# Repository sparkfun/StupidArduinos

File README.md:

# StupidArduinos

Stupid Arduino is the practice of designing elaborate and pointless implementations of the Arduino platform. I chose Arduino as the phrase on which I would be free-style improvising for a few reasons. First of all, it’s a popular and accessible platform — far fewer people would be excited about stupid implementations of, say, HyperCard. Secondly, the ingredients for an “Arduino” (in the generic sense) are few and well defined: Any microcontroller with accessible GPIO running the Arduino bootloader can be reasonably referred to as an Arduino. And finally, it’s a platform that comprises multiple disciplines: An Arduino can be “stupid” because of its controller, its electrical design, its mechanical design or even its firmware or bootloader design. 

Stupid Arduino only has three rules: 

1) The device must run a functional, Arduino-flavored bootloader
2) It has to execute the example “blink” sketch (with appropriate delays)
3) It must have some form of GPIO broken out from the controller

Beyond that, anything goes: fun clock speeds, clock sources, architectures, form factors, power management - it’s all fair game.

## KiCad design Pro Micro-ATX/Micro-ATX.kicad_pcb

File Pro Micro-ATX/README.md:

<h2>The RedBoard Pro Micro-ATX</h2>

Let me show you its features:

1) Convenient and well-supported Micro-ATX form factor

The Micro-ATX form factor is compatible not only with Micro-ATX PC cases but also Standard- and Extended-ATX cases. The Pro Micro-ATX conforms to the mechanical specs for footprint size, stand-off placement and expansion card position for the widest possible compatibility across case manufacturers.

2) Support for enthusiast-grade cooling hardware

The heart of the Pro Micro-ATX is an ATmega32u4 microcontroller that has been positioned (along with the necessary support components) within the mechanical footprint of an LGA 1151 socket. This gives the user a wide array of options for (pointlessly) cooling the microcontroller, including many AIO air and liquid coolers designed for modern Intel processors.

3) 24-pin ATX power support

Arguably the only useful feature on this board is the 24-pin power connector, which allows the ATmega32u4 and its peripherals to draw from any external, ATX-compatible power supply.

4) Expanded EEPROM

You may be surprised to find that I had, uh, some room on the board. I decided that one way of utilizing this space might be to stack as many I²C EEPROM chips as I could on the one available bus. That number turns out to be eight (with capacities up to 512k), giving this board a whopping 2Mbits of storage! I stopped just short of Shawn’s suggestion of laying out I²C DIMM footprints and compatible “RAM cards,” because you have to draw the line somewhere…

5) Card Slots!!!

…but NOT at expansion cards! After all, what’s a motherboard layout without expansion slots? It’s not enthusiast-grade, that’s for sure. So I created a system of expansion cards for the Pro Micro-ATX. It could be argued that the Arduino already has a system of expansion cards — shields — and that they are the best possible expansion system given that they have access to literally every I/O of the host controller. I decided that there was no electrical improvement to be made here and that, instead, adapting the shield system to the ATX form factor would be my main focus. I found the idea of using PCI connectors a little excessive, even for an undertaking of this magnitude, and opted for a smaller 28 Position Card Edge Connector. The compatible cards adapt the pinout of the edge connector back to the familiar Arduino shield form factor, so any existing shield can be connected and accessed through the expansion slots in the back of the case.

6) Rear I/O

Any good motherboard has rear I/O and the Pro Micro-ATX is no exception. Accessible from the rear panel are a standard shield footprint, a 6-pin Atmel ISP header and a USB type-B connector for serial communication.

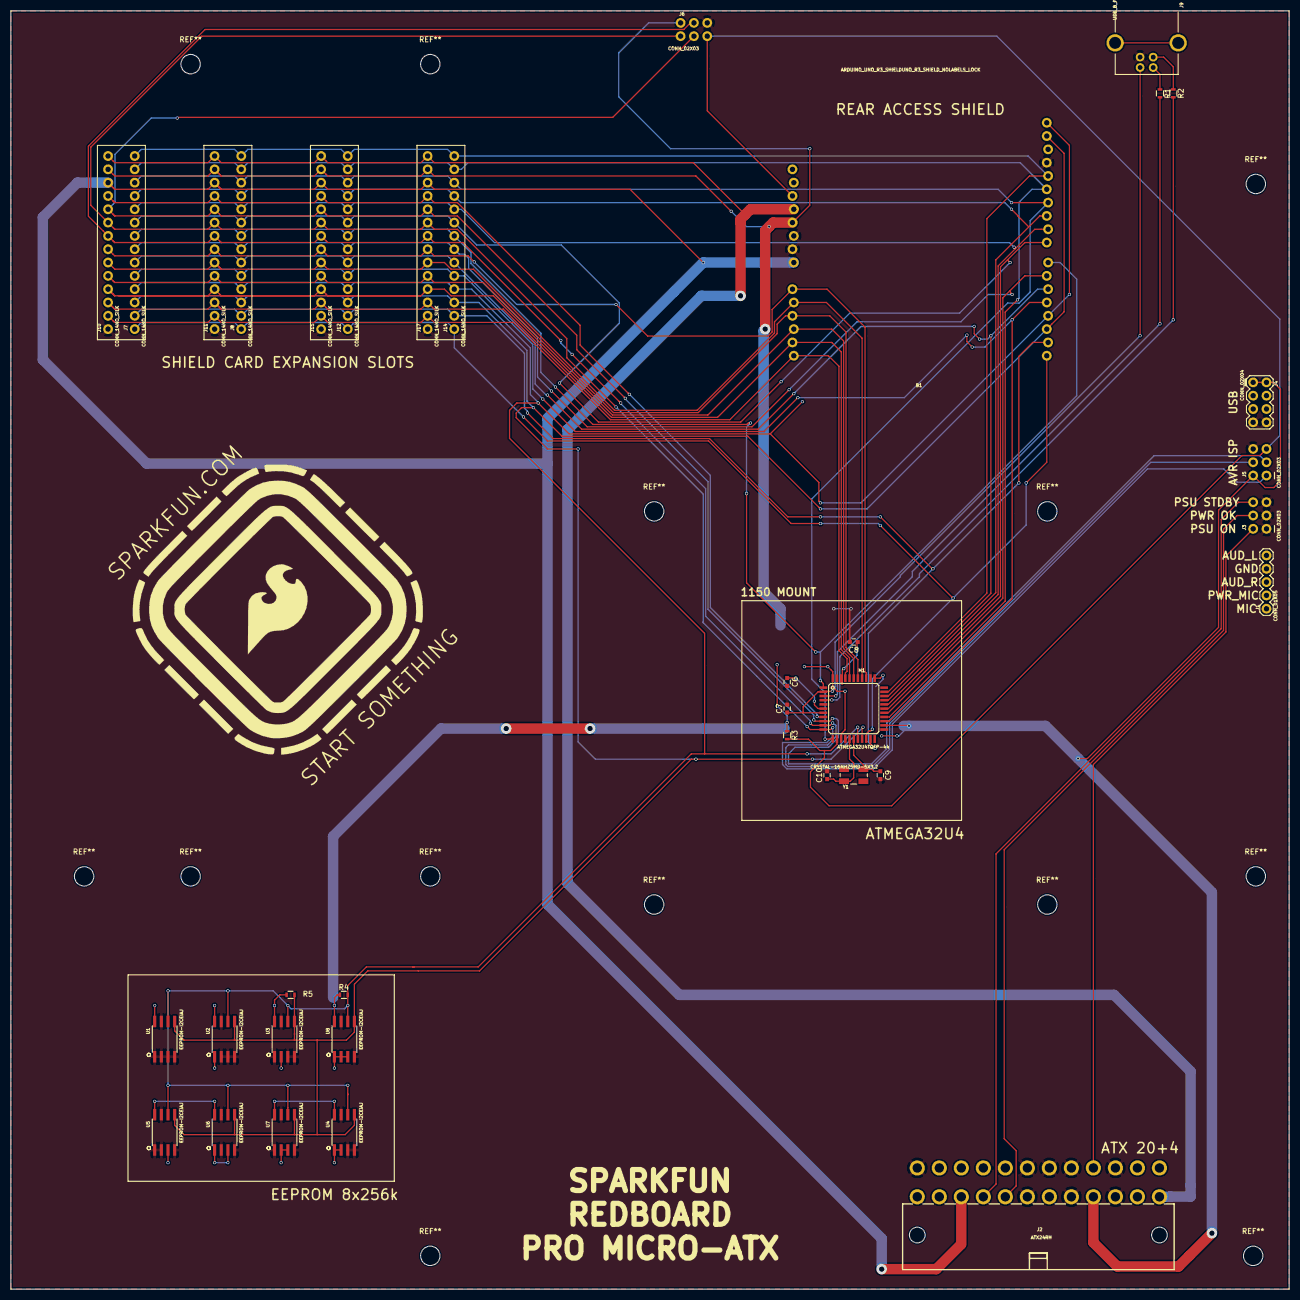
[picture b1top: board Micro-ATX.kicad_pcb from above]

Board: 2 copper layers, 243.8 x 243.8 mm, 36 parts (0 on the bottom side), 43 nets.

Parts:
B1: ARDUINO_UNO_R3_SHIELDUNO_R3_SHIELD_NOLABELS_LOCK; UNO_R3_SHIELD_NOLABELS_LOCK
C6, C7: 1.0UF-0603-16V-10%; C_0603
C8: 0.1UF-0603-100V-10%; C_0603
C9, C10: 22PF-0603-50V-5%; C_0603
J1: CONN_01X05; 1X05
J2: ATX24RH; ATX24_RIGHT_ANGLE
J3, J5, J6: CONN_02X03; 2X3-NS
J4: CONN_02X04; 2X4
J7, J8, J10, J11, J12, J14, J15, J17: CONN_14NO_SILK; 1X14_NO_SILK
J9: USB_B_PTH; USB-B-PTH
M1: ATMEGA32U4TQFP-44; TQFP44
R1, R2: 22OHM; R_0603
R3: 10KOHM-0603-1_10W-1%; R_0603
R4, R5: 4.7KOHM; R_0603
U1, U2, U3, U4, U5, U6, U7, U8: EEPROM-I2CEIAJ; SO08-EIAJ
Y1: CRYSTAL-16MHZSMD-5X3.2; CRYSTAL-SMD-5X3.2-4PAD

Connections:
3.3V: B1.3.3V, J2.1, J10.14, J11.14, J15.14, J17.14
5V: B1.5V, J2.4, J4.1, J4.2, J5.2, J6.2, J10.13, J11.13, J15.13, J17.13, M1.14, M1.24, M1.34, M1.44, R3.1, R4.1, R5.1, U1.8, U2.1, U2.8, U3.2, U3.8, U4.1, U4.2, U4.8, U5.3, U5.8, U6.1, U6.3, U6.8, U7.2, U7.3, U7.8, U8.1, U8.2, U8.3, U8.8
12V: B1.VIN, J2.10, J10.12, J11.12, J15.12, J17.12
/A0: B1.A0, J10.7, J11.7, J15.7, J17.7, M1.36
/A1: B1.A1, J10.6, J11.6, J15.6, J17.6, M1.37
/A2: B1.A2, J10.5, J11.5, J15.5, J17.5, M1.38
/A3: B1.A3, J10.4, J11.4, J15.4, J17.4, M1.39
/A4: B1.A4, J10.3, J11.3, J15.3, J17.3, M1.40
/A5: B1.A5, J10.2, J11.2, J15.2, J17.2, M1.41
/D0: B1.RX, J7.1, J8.1, J12.1, J14.1, M1.20
/D1: B1.TX, J7.2, J8.2, J12.2, J14.2, M1.21
/D2: B1.D2, B1.SDA, J7.3, J8.3, J12.3, J14.3, M1.19, R5.2, U1.5, U2.5, U3.5, U4.5, U5.5, U6.5, U7.5, U8.5
/D3: B1.D3, B1.SCL, J7.4, J8.4, J12.4, J14.4, M1.18, R4.2, U1.6, U2.6, U3.6, U4.6, U5.6, U6.6, U7.6, U8.6
/D4: B1.D4, J7.5, J8.5, J12.5, J14.5, M1.25
/D5: B1.D5, J7.6, J8.6, J12.6, J14.6, M1.31
/D6: B1.D6, J7.7, J8.7, J12.7, J14.7, M1.27
/D7: B1.D7, J7.8, J8.8, J12.8, J14.8, M1.1
/D8: B1.D8, J7.9, J8.9, J12.9, J14.9, M1.28
/D9: B1.D9, J7.10, J8.10, J12.10, J14.10, M1.29
/D10: B1.D10, J7.11, J8.11, J12.11, J14.11, M1.30
/D11: B1.D11, J7.12, J8.12, J12.12, J14.12, M1.12
/D12: B1.D12, J7.13, J8.13, J12.13, J14.13, M1.26
/D13: B1.D13, J7.14, J8.14, J12.14, J14.14, M1.32
/D+: M1.4, R2.2
/D-: M1.3, R1.2
/MISO: J5.1, J6.1, J10.9, J11.9, J15.9, J17.9, M1.11
/MOSI: J5.4, J6.4, J10.8, J11.8, J15.8, J17.8, M1.10
/PS_ON: J2.16, J3.2
/PWR_OK: J2.8, J3.4
/RESET: B1.RES, J5.5, J6.5, M1.13, R3.2
/SCK: J5.3, J6.3, J10.10, J11.10, J15.10, J17.10, M1.9
/SS: J10.11, J11.11, J15.11, J17.11, M1.8
/STDBY: J2.9, J3.6
/USB+: J4.5, J4.6
/USB-: J4.3, J4.4
/UVCC: C7.1, J9.VBUS, M1.2, M1.7
GND: B1.GND@, C6.2, C7.2, C8.2, C9.2, C10.2, J1.4, J2.3, J2.5, J2.7, J2.15, J2.17, J2.18, J2.19, J2.24, J3.1, J3.3, J3.5, J4.7, J4.8, J5.6, J6.6, J9.GND, J10.1, J11.1, J15.1, J17.1, M1.5, M1.15, M1.23, M1.35, M1.43, U1.1, U1.2, U1.3, U1.4, U1.7, U2.2, U2.3, U2.4, U2.7, U3.1, U3.3, U3.4, U3.7, U4.3, U4.4, U4.7, U5.1, U5.2, U5.4, U5.7, U6.2, U6.4, U6.7, U7.1, U7.4, U7.7, U8.4, U8.7
unnamed: C6.1, M1.6
unnamed: C8.1, M1.42
unnamed: C9.1, M1.17, Y1.1
unnamed: C10.1, M1.16, Y1.3
unnamed: J9.D+, R2.1
unnamed: J9.D-, R1.1

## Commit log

2017-12-19 Add project photo
